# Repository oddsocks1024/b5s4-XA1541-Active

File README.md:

# b5s4-XA1541-Active
Read &amp; Write C64, C128 and VIC-20 disks directly on a PC using a Commodore drive

## Description

This is the b5s4 PCB version of the XA1541 Active adapter. It lets you connect Commodore Floppy Disk drives to a PC with a Parallel
Port and read and write to those disks natively. See: https://sta.c64.org/xa1541.html for additional information.

**Compatible Floppy Drives**

* Commodore 1541
* Commodore 1541-II
* Commodore 1570
* Commodore 1571
* Commodore 1581
* ... and compatibles

**Compatible Software**

* The Star Commander
* OpenCBM
* NibTools
* CMBXfer
* Mtap & Ptap
* NIBTools
* cbm4linux

## Bill of Materials

| Qty | Component                                          |
|:---:|----------------------------------------------------|
| 1   | Female DIN45322 connector                          |
| 1   | Male DB25 connector - straight - for edge mounting |
| 4   | 2N3904 transistors                                 |
| 4   | 4.7KΩ Axial Resistors - 1/4 watt                   |

## 3D Printable Case
A 3D printable case specifically designed for this PCB is also available. STLs are included in this repo and there is also a [Thingiverse Page](https://www.thingiverse.com/thing:7099785)

* Designed to use screws as they produce a much nicer, more robust case
* 4 x 3.5mm self-tapping screws to attach the shells. Max length about 12mm

## Support Me
* [My Projects](https://projects.amiga-hardware.com) - Donate on this page
* [Order the PCB](https://www.pcbway.com/project/shareproject/b5s5_XA1541_Active_Read_Write_C64_C128_VIC20_disks_on_PC_ddd3c031.html)
* [Order the Case](https://www.pcbway.com/project/shareproject/b5s4_XA1541_Active_Case_Slimline_af867c8e.html)

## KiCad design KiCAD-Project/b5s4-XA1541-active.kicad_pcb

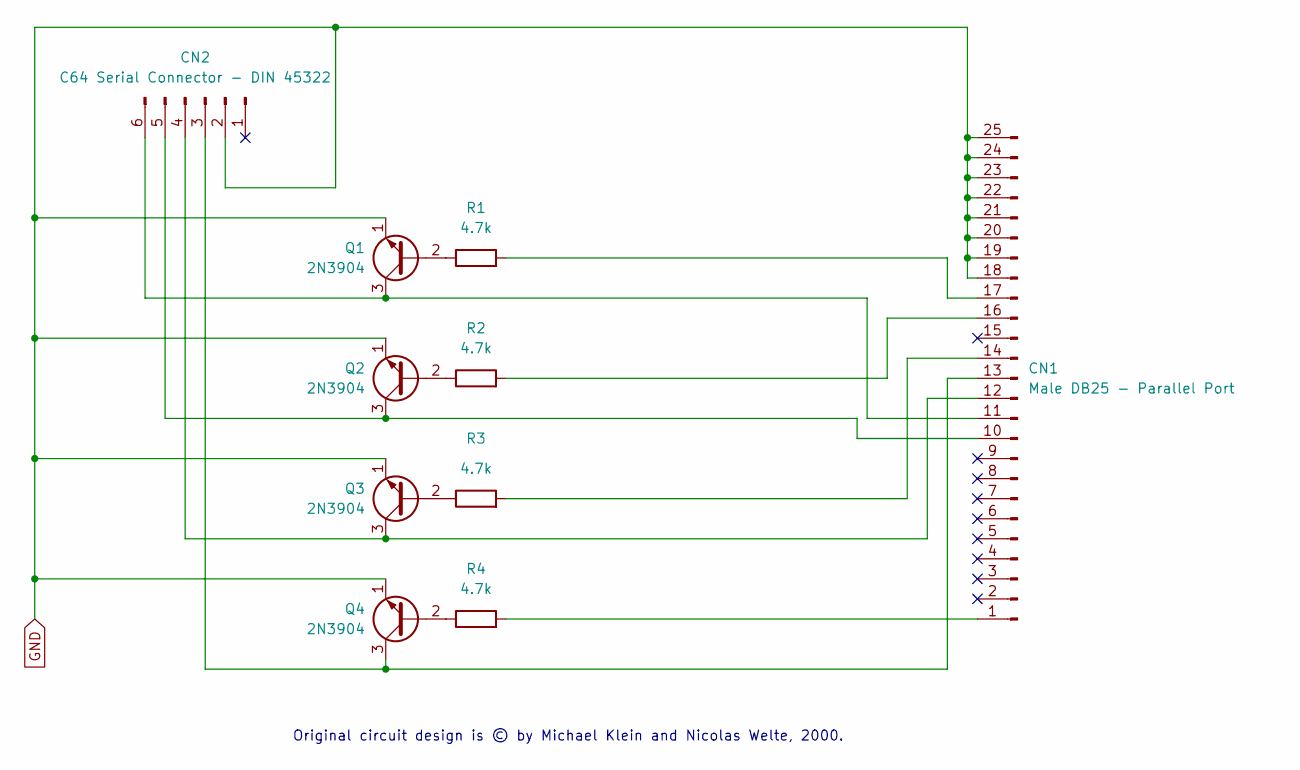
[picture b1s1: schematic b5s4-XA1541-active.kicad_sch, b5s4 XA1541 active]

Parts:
CN1: Male DB25 - Parallel Port; DSUB-25_Pins_EdgeMount_P2.77mm
CN2: C64 Serial Connector - DIN 45322; C64 Serial Connector
Q1, Q2, Q3, Q4: 2N3904; TO-92_Inline
R1, R2, R3, R4: 4.7k; R_Axial_DIN0207_L6.3mm_D2.5mm_P10.16mm_Horizontal

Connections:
GND: CN1.18, CN1.19, CN1.20, CN1.21, CN1.22, CN1.23, CN1.24, CN1.25, CN2.2, Q1.1 (E), Q2.1 (E), Q3.1 (E), Q4.1 (E)
unnamed: CN1.1, R4.2
unnamed: CN1.10, CN2.5, Q2.3 (C)
unnamed: CN1.11, CN2.6, Q1.3 (C)
unnamed: CN1.12, CN2.4, Q3.3 (C)
unnamed: CN1.13, CN2.3, Q4.3 (C)
unnamed: CN1.14, R3.2
unnamed: CN1.16, R2.2
unnamed: CN1.17, R1.2
unnamed: Q1.2 (B), R1.1
unnamed: Q2.2 (B), R2.1
unnamed: Q3.2 (B), R3.1
unnamed: Q4.2 (B), R4.1

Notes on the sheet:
Original circuit design is © by Michael Klein and Nicolas Welte, 2000.

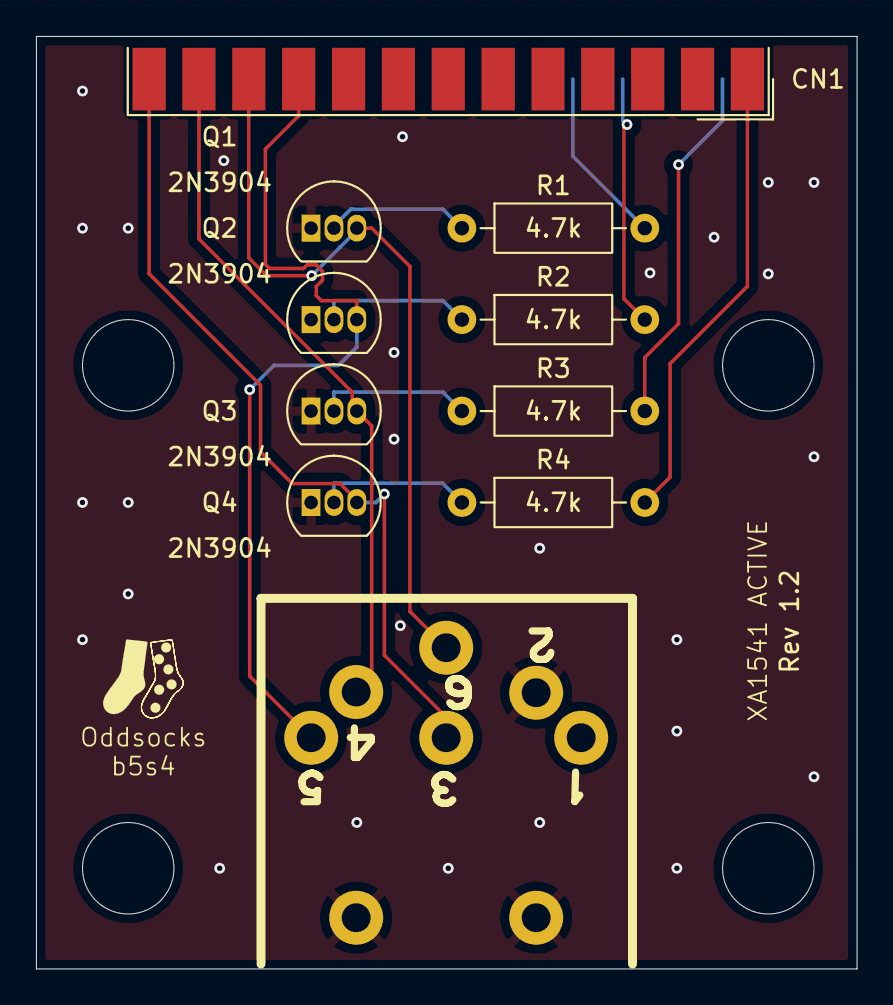
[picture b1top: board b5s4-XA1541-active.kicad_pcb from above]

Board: 2 copper layers, 45.6 x 51.8 mm, 10 parts (0 on the bottom side), 13 nets.

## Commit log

2025-11-09 Added gerbers and updated README.md
2025-11-30 Add license file
2025-11-30 Added PDF schematics

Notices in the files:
KiCAD-Project/b5s4-XA1541-active.kicad_pcb:
Original Circuit Design © 2000
